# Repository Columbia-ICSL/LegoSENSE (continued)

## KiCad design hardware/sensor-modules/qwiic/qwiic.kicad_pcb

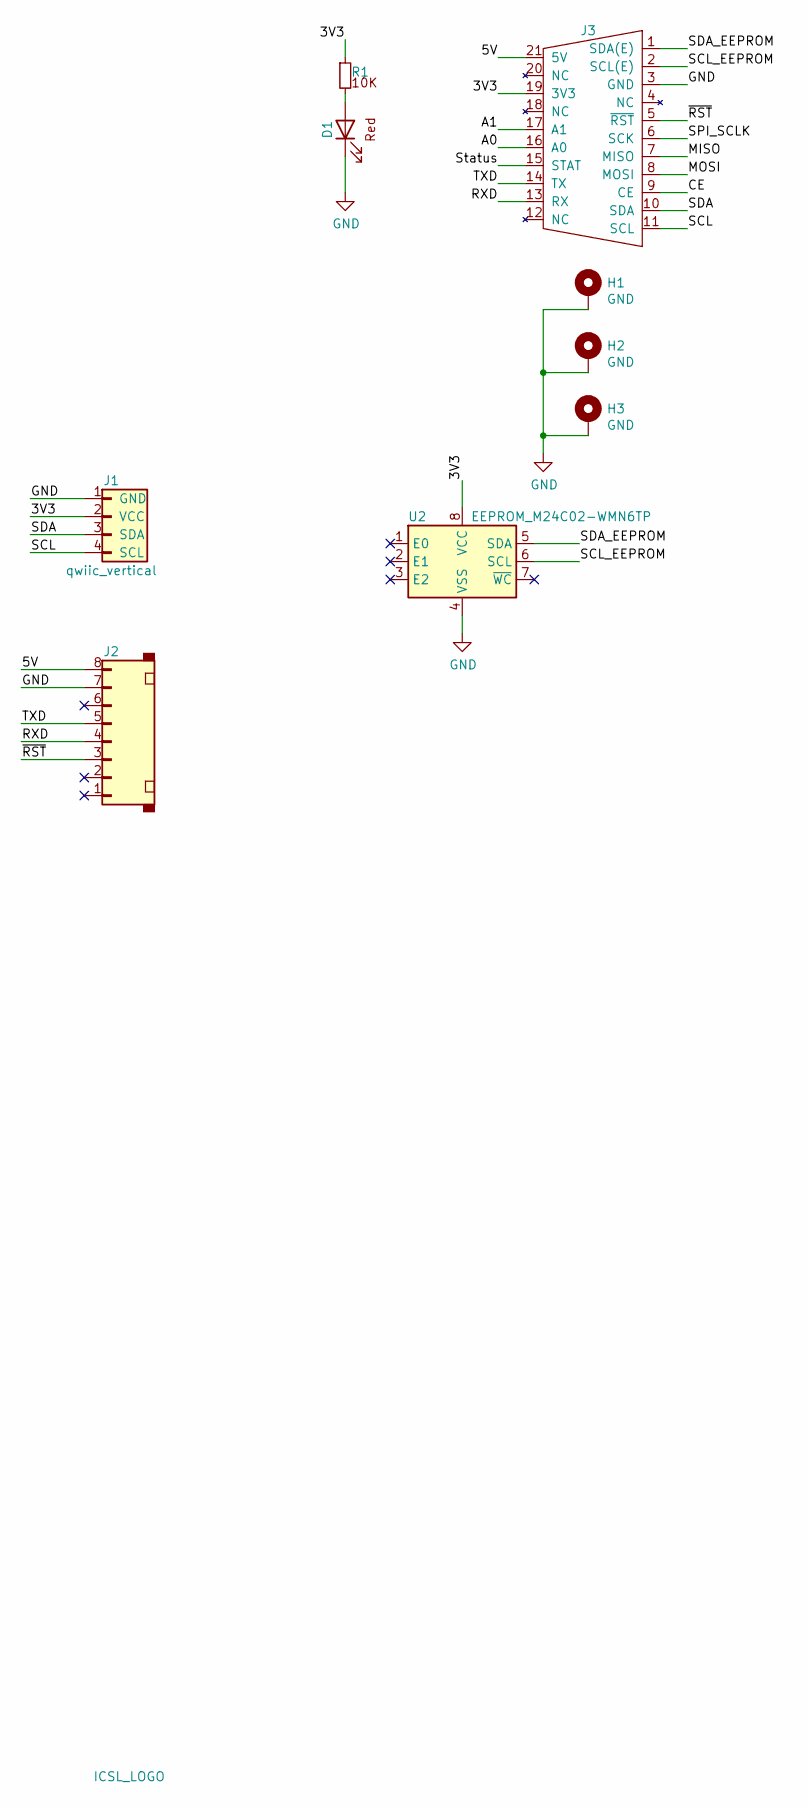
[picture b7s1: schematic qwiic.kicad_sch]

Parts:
D1: LED_0603_Red; LED_0603_1608Metric; MFR Part# KT-0603R; LCSC C2286
H1, H2, H3: GND; M1502-B-2545-AL-TOP
J1: qwiic_vertical; JST_SH_1x04_1.00mm_Vertical; MFR Part# C145961; LCSC C145961
J2: 1.25mm_8P_SMD_Vertical; Molex_PicoBlade_53398-0871_1x08-1MP_P1.25mm_Vertical; MFR Part# AFC12-S08CCC-00; LCSC C395349
J3: Amphenol_91911-31321_plug; Amphenol_91911-31321LF_PLUG; LCSC C9900009023
R1: R_0402_10K; R_0402_1005Metric; MFR Part# 0402WGF1002TCE; LCSC C25744
U1: ICSL_LOGO; icsl_logo
U2: EEPROM_M24C02-WMN6TP; SOIC-8_3.9x4.9mm_P1.27mm; MFR Part# M24C02-WMN6TP; LCSC C7562

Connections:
/3V3: J1.2 (VCC), J3.19 (3V3), R1.1, U2.8 (VCC)
/5V: J2.8, J3.21 (5V)
/A0: J3.16 (A0)
/A1: J3.17 (A1)
/CE: J3.9 (CE)
/MISO: J3.7 (MISO)
/MOSI: J3.8 (MOSI)
/RXD: J2.4, J3.13 (RX)
/SCL: J1.4 (SCL), J3.11 (SCL)
/SCL_EEPROM: J3.2 (SCL(E)), U2.6 (SCL)
/SDA: J1.3 (SDA), J3.10 (SDA)
/SDA_EEPROM: J3.1 (SDA(E)), U2.5 (SDA)
/SPI_SCLK: J3.6 (SCK)
/Status: J3.15 (STAT)
/TXD: J2.5, J3.14 (TX)
/~RST: J2.3, J3.5 (~RST)
GND: D1.1 (K), H1.1, H2.1, H3.1, J1.1 (GND), J2.7, J3.3 (GND), U2.4 (VSS)
unnamed: D1.2 (A), R1.2

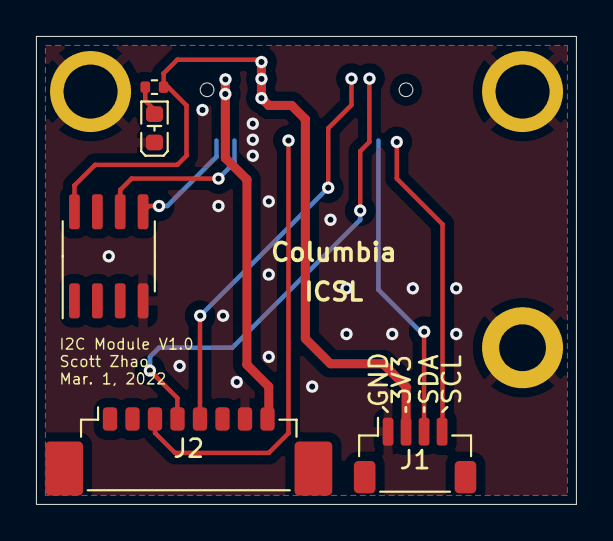
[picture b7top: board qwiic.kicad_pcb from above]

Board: 4 copper layers, 30.0 x 26.0 mm, 10 parts (1 on the bottom side), 11 nets.

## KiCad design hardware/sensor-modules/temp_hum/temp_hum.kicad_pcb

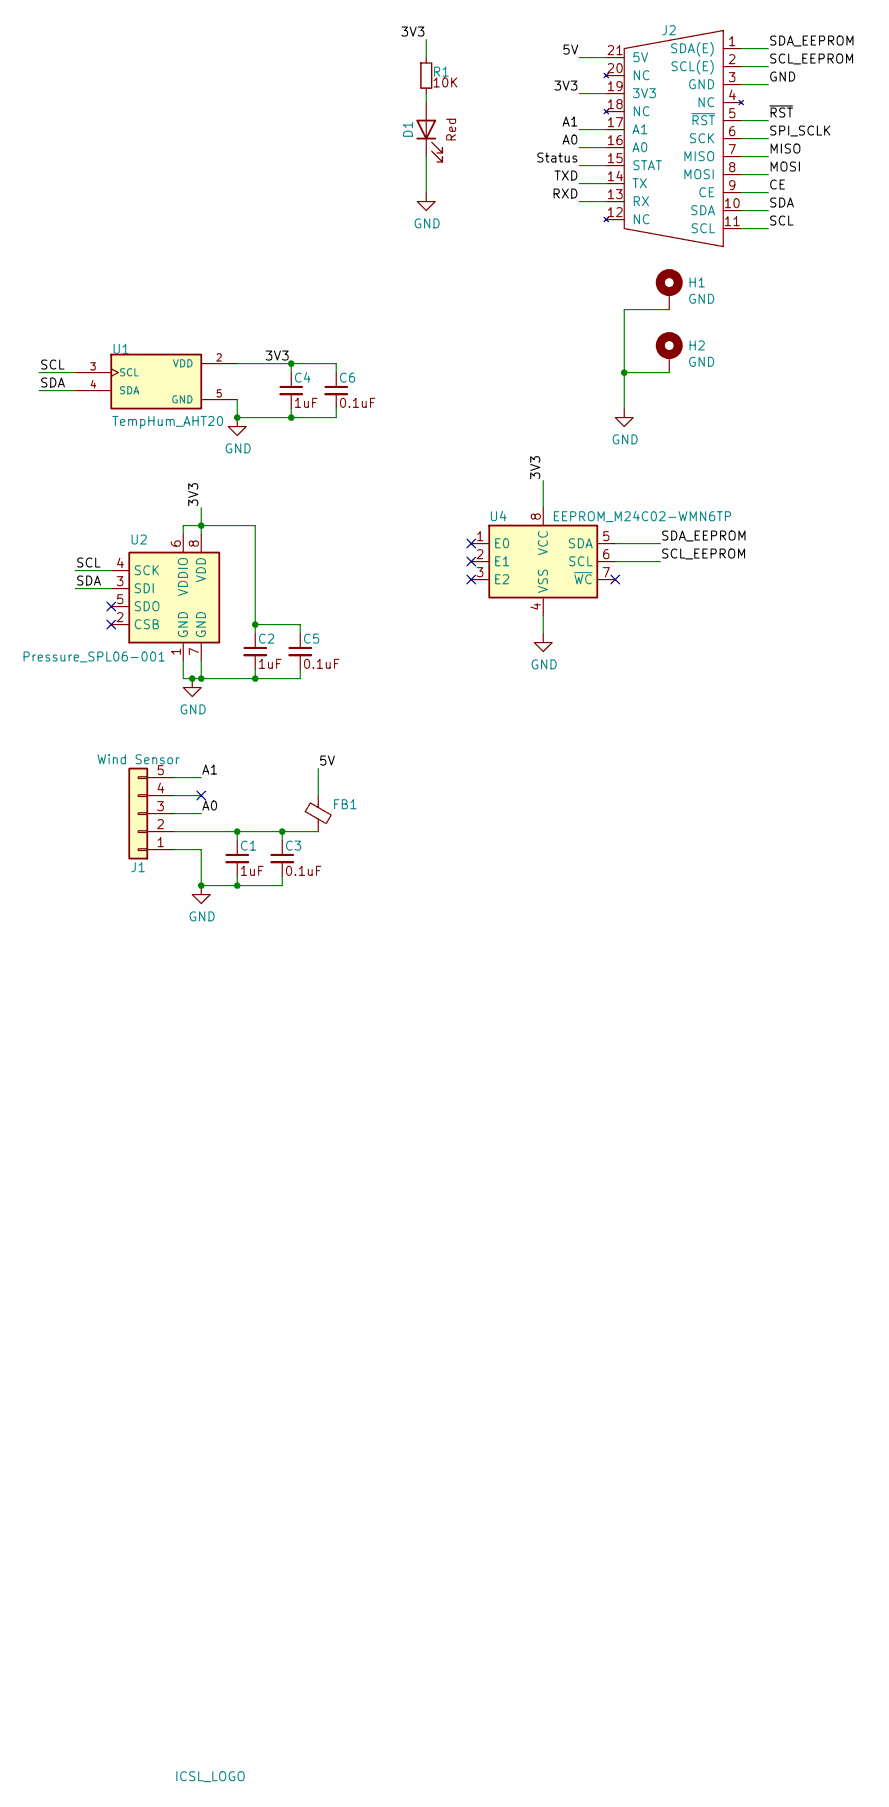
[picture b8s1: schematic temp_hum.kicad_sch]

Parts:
C1, C2, C4: C_0402_1uF_25V; C_0402_1005Metric; MFR Part# CL05A105KA5NQNC; LCSC C52923
C3, C5, C6: C_0402_0.1uF_16V; C_0402_1005Metric; MFR Part# CL05B104KO5NNNC; LCSC C1525
D1: LED_0603_Red; LED_0603_1608Metric; MFR Part# KT-0603R; LCSC C2286
FB1: B_0805_600R; L_0805_2012Metric; MFR Part# GZ2012D601TF; LCSC C1017
H1, H2: GND; M1502-B-2545-AL-TOP
J1: Wind Sensor; PinHeader_1x05_P2.54mm_Vertical
J2: Amphenol_91911-31321_plug; Amphenol_91911-31321LF_PLUG; LCSC C9900009023
R1: R_0402_10K; R_0402_1005Metric; MFR Part# 0402WGF1002TCE; LCSC C25744
U1: TempHum_AHT20; AHT20; MFR Part# AHT20; LCSC C2757850
U2: Pressure_SPL06-001; SPL06-001; MFR Part# SPL06-001; LCSC C2684428
U3: ICSL_LOGO; icsl_logo
U4: EEPROM_M24C02-WMN6TP; SOIC-8_3.9x4.9mm_P1.27mm; MFR Part# M24C02-WMN6TP; LCSC C7562

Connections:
/3V3: C2.1, C4.1, C5.1, C6.1, J2.19 (3V3), R1.1, U1.2 (VDD), U2.6 (VDDIO), U2.8 (VDD), U4.8 (VCC)
/5V: FB1.1, J2.21 (5V)
/A0: J1.3, J2.16 (A0)
/A1: J1.5, J2.17 (A1)
/CE: J2.9 (CE)
/MISO: J2.7 (MISO)
/MOSI: J2.8 (MOSI)
/RXD: J2.13 (RX)
/SCL: J2.11 (SCL), U1.3 (SCL), U2.4 (SCK)
/SCL_EEPROM: J2.2 (SCL(E)), U4.6 (SCL)
/SDA: J2.10 (SDA), U1.4 (SDA), U2.3 (SDI)
/SDA_EEPROM: J2.1 (SDA(E)), U4.5 (SDA)
/SPI_SCLK: J2.6 (SCK)
/Status: J2.15 (STAT)
/TXD: J2.14 (TX)
/~RST: J2.5 (~RST)
GND: C1.2, C2.2, C3.2, C4.2, C5.2, C6.2, D1.1 (K), H1.1, H2.1, J1.1, J2.3 (GND), U1.5 (GND), U2.1 (GND), U2.7 (GND), U4.4 (VSS)
unnamed: C1.1, C3.1, FB1.2, J1.2
unnamed: D1.2 (A), R1.2

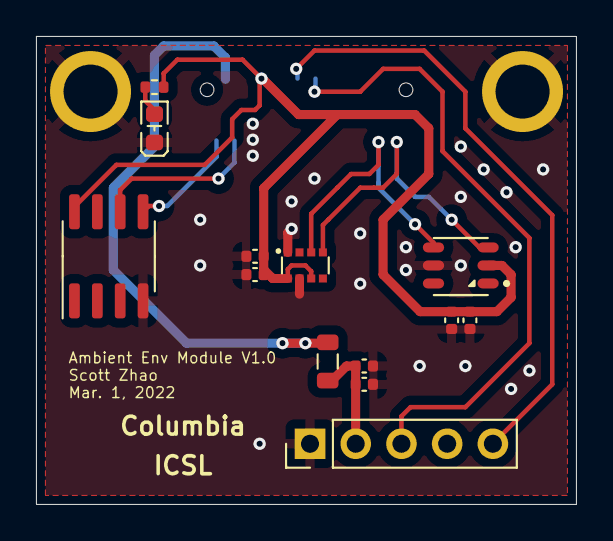
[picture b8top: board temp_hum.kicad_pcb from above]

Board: 4 copper layers, 30.0 x 26.0 mm, 17 parts (1 on the bottom side), 11 nets.

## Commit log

2023-03-06 add module and dev PCB files
2023-03-06 add kicad library submodule
2023-03-06 cleanup
2023-03-06 add hardware readme
2023-03-06 cleanup dev board type 1
2023-03-06 cleanup dev board type 2
2023-03-07 cleanup dev board type 3
2023-03-07 update hw readme
2023-03-08 update hw readme; add template PCB
2023-03-08 add template board screenshot
2023-03-08 add carrier board; update readme
2023-05-12 add software submodule
2023-05-12 update main readme
